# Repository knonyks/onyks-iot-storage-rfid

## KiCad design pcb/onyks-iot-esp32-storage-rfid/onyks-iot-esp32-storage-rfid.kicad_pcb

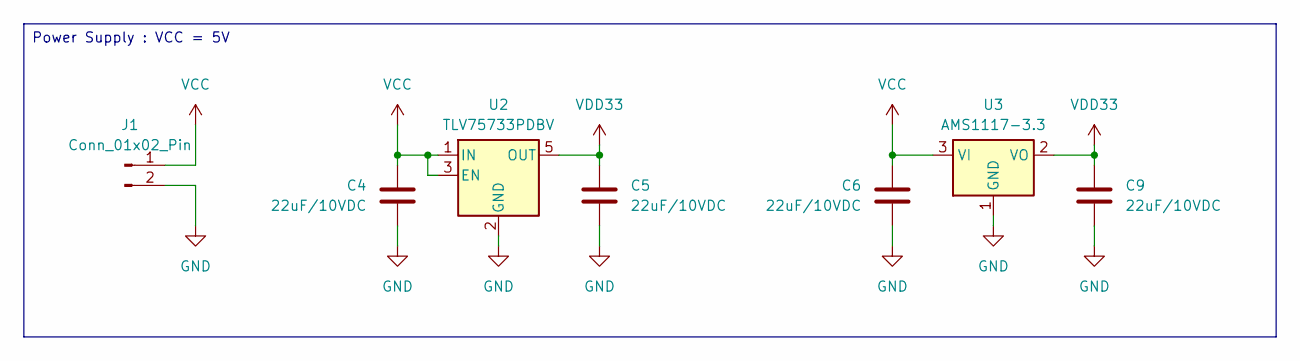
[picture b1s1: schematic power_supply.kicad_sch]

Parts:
C4, C5, C6, C9: 22uF/10VDC; C_0603_1608Metric_Pad1.08x0.95mm_HandSolder
J1: Conn_01x02_Pin; PinHeader_1x02_P2.54mm_Vertical
U2: TLV75733PDBV; SOT-23-5
U3: AMS1117-3.3; SOT-223-3_TabPin2

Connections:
GND: C4.2, C5.2, C6.2, C9.2, J1.2, U2.2 (GND), U3.1 (GND); also elsewhere on the board
VCC: C4.1, C6.1, J1.1, U2.1 (IN), U2.3 (EN), U3.3 (VI); also elsewhere on the board
VDD33: C5.1, C9.1, U2.5 (OUT), U3.2 (VO); also elsewhere on the board

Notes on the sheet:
Power Supply : VCC = 5V

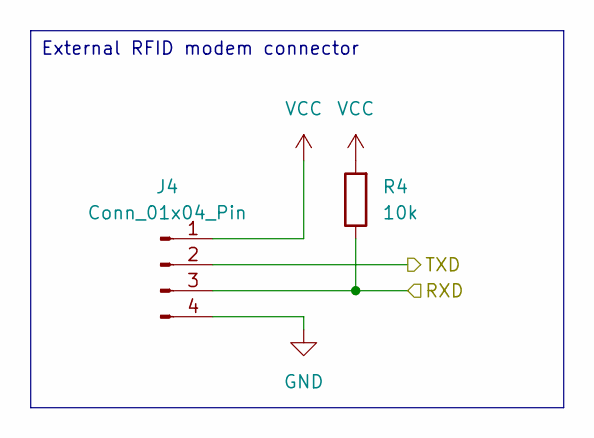
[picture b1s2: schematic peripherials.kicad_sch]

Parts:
J4: Conn_01x04_Pin; PinHeader_1x04_P2.54mm_Vertical
R4: 10k; R_0603_1608Metric_Pad0.98x0.95mm_HandSolder

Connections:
/ESP32/RXD: J4.2; also elsewhere on the board
/ESP32/TXD: J4.3, R4.1; also elsewhere on the board
GND: J4.4; also elsewhere on the board
VCC: J4.1, R4.2; also elsewhere on the board

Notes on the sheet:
External RFID modem connector

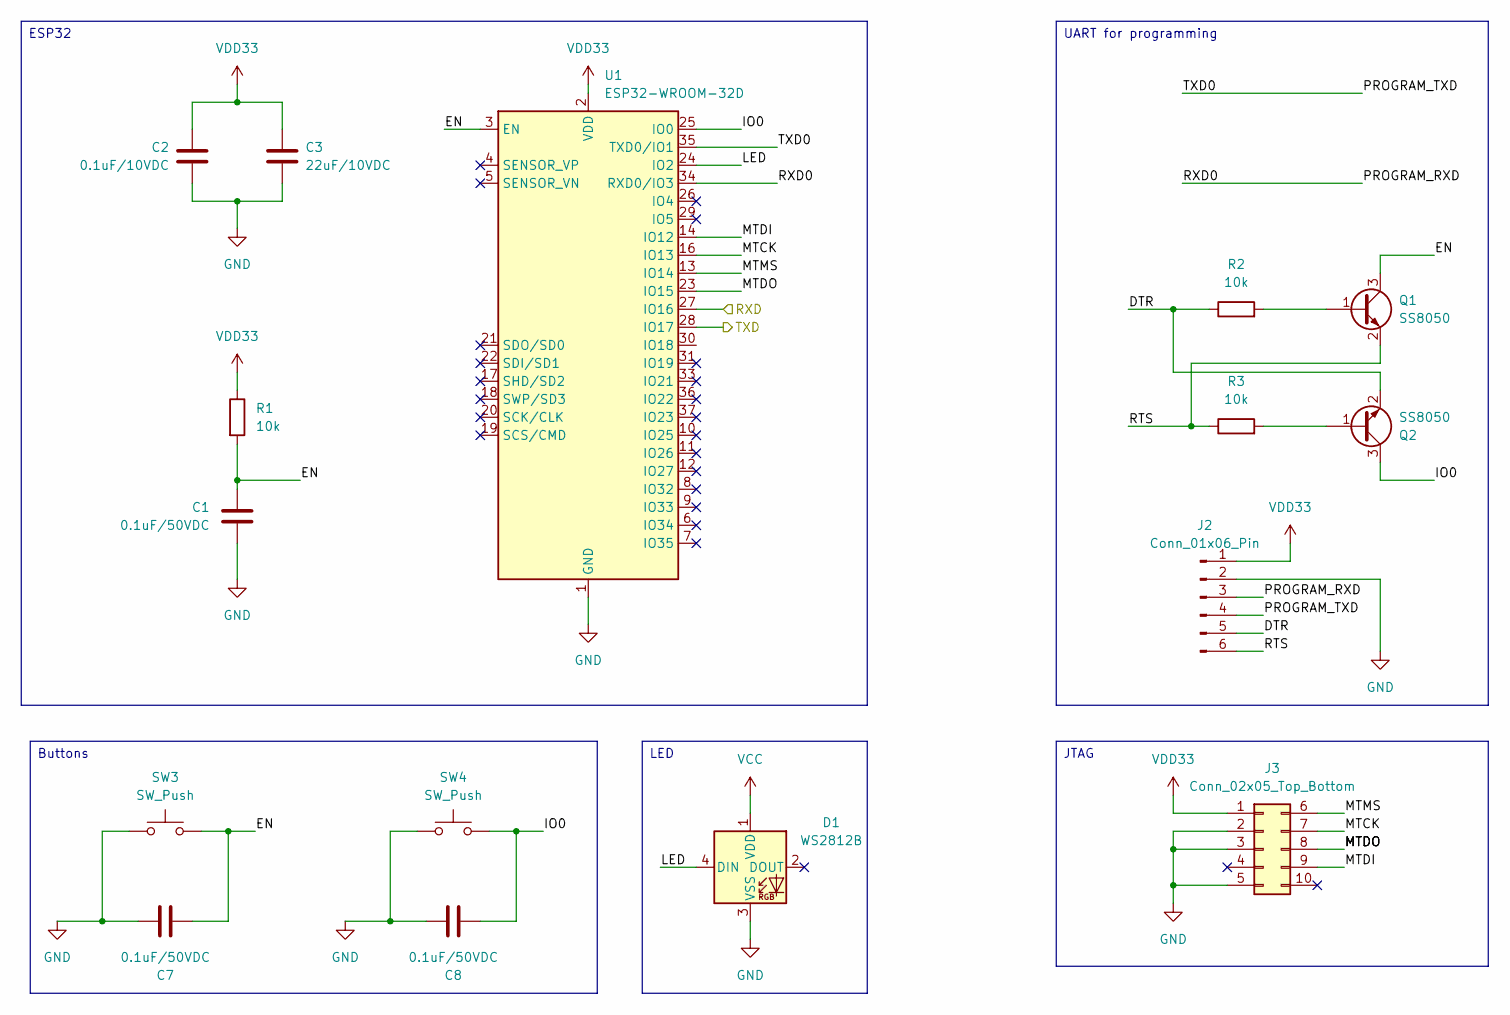
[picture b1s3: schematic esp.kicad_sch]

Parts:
C1, C7, C8: 0.1uF/50VDC; C_0603_1608Metric_Pad1.08x0.95mm_HandSolder
C2: 0.1uF/10VDC; C_0603_1608Metric_Pad1.08x0.95mm_HandSolder
C3: 22uF/10VDC; C_0603_1608Metric_Pad1.08x0.95mm_HandSolder
D1: WS2812B; LED_WS2812B_PLCC4_5.0x5.0mm_P3.2mm
J2: Conn_01x06_Pin; PinHeader_1x06_P2.54mm_Vertical
J3: Conn_02x05_Top_Bottom; PinHeader_2x05_P2.54mm_Vertical
Q1, Q2: SS8050; SOT-23
R1, R2, R3: 10k; R_0603_1608Metric_Pad0.98x0.95mm_HandSolder
SW3, SW4: SW_Push; SW_Tactile_SPST_NO_Straight_CK_PTS636Sx25SMTRLFS
U1: ESP32-WROOM-32D

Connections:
/ESP32/DTR: J2.5, Q2.2 (E), R2.1
/ESP32/EN: C1.2, C7.2, Q1.3 (C), R1.2, SW3.2, U1.3 (EN)
/ESP32/IO0: C8.2, Q2.3 (C), SW4.2, U1.25 (IO0)
/ESP32/LED: D1.4 (DIN), U1.24 (IO2)
/ESP32/MTCK: J3.7, U1.16 (IO13)
/ESP32/MTDI: J3.9, U1.14 (IO12)
/ESP32/MTDO: J3.8, U1.23 (IO15)
/ESP32/MTMS: J3.6, U1.13 (IO14)
/ESP32/PROGRAM_RXD: J2.3, U1.34 (RXD0/IO3)
/ESP32/PROGRAM_TXD: J2.4, U1.35 (TXD0/IO1)
/ESP32/RTS: J2.6, Q1.2 (E), R3.1
/ESP32/RXD: U1.27 (IO16); also elsewhere on the board
/ESP32/TXD: U1.28 (IO17); also elsewhere on the board
GND: C1.1, C2.2, C3.2, C7.1, C8.1, D1.3 (VSS), J2.2, J3.2, J3.3, J3.5, SW3.1, SW4.1, U1.1 (GND), U1.15 (GND), U1.38 (GND), U1.39 (GND); also elsewhere on the board
unnamed: Q1.1 (B), R2.2
unnamed: Q2.1 (B), R3.2
VCC: D1.1 (VDD); also elsewhere on the board
VDD33: C2.1, C3.1, J2.1, J3.1, R1.1, U1.2 (VDD); also elsewhere on the board

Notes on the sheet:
LED
UART for programming
Buttons
JTAG
ESP32

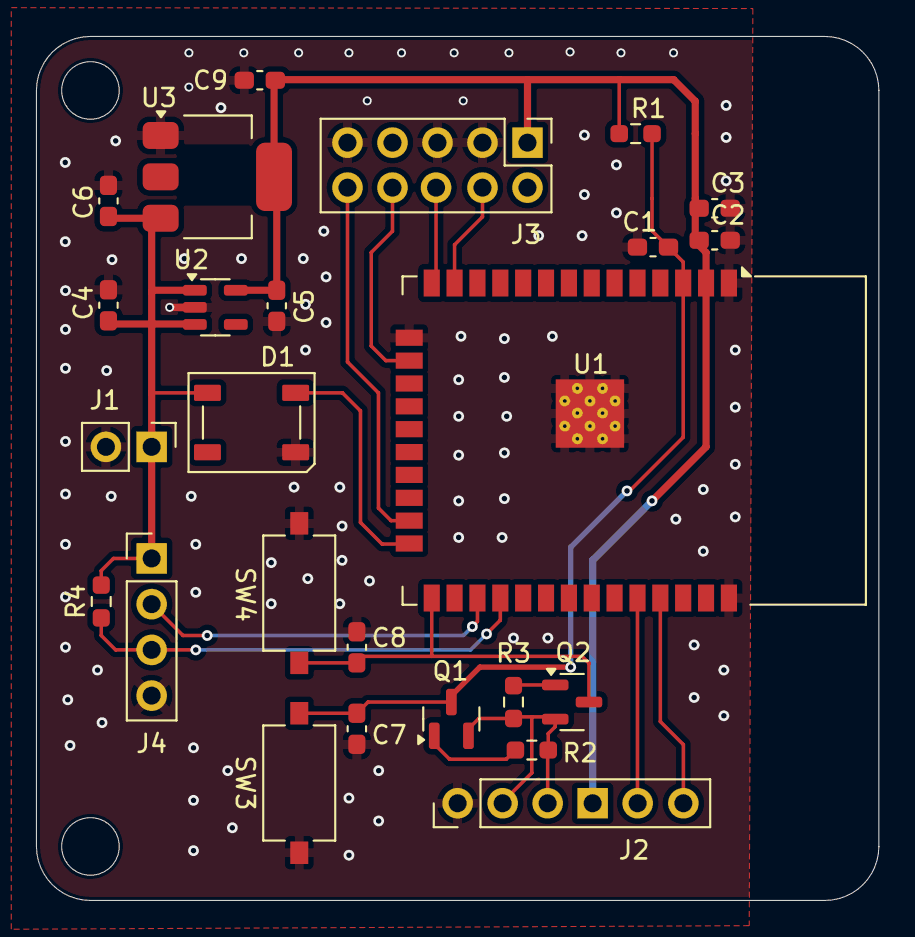
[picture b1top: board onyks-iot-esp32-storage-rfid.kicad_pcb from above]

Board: 4 copper layers, 46.8 x 48.0 mm, 25 parts (0 on the bottom side), 18 nets.

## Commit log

2025-06-27 Pierwszy commit
2025-07-28 Nie pełna lista elementów wykorzystywanych w projekcie. Zrobiony schemat (bez rewizii).
2025-07-28 Zapomniałem o rulesach.
2025-08-20 oznaczenie pinów i podział elementów PCB
    dodanie oznaczenia nieużywanych pinów zgodnie z opinią schematu
2025-08-23 ustawienie i połączenia na PCB
    szerokości ścieżek i wielkości przelotek jeszcze do poprawy
2025-08-31 szerokości ścieżek
2025-09-09 PCB gotowe do review
2025-10-22 projekt PCB v2
2025-10-23 projekt PCB v2.2
    Projekt gotowy do review. @przemech @Xenon02
    Dodany zostal drugi stabilizator AMS1117-3.3, ktory mamy w nadmiarze w kole.
    Zaktualizowano DR na zgodne z JLCPCB capabilities, ktore wczesniej byly bledne.
    Dodano opis wymiarow plytki.
2025-10-23 zrobione review, wprowadzone poprawki, czeka na ostatnie sprawdzenie jak prezes bedzie bardizej przytomny
2025-10-26 Adding Gerber files
2025-10-29 male zmiany PCB
    poprawiono niezmienione przelotki i usunieto powierzchnie masy pod U3
2025-11-16 Aktualizacja gerberów, powiązane z dwoma poprzednimi commit-ami
2025-11-16 Poprawka folderu gdzie gerbery zostały włożone (/pcb/onyks-iot-esp32-storage-rfid/Fabrication a powinno być /Fabrication)
2026-03-23 dokumentacja plytki v1.0
2026-03-23 dokumentacja v1.1
    dodanie zdjęcia płytki PCB i poprawa adresacji pliku BOM.html
2026-04-15 kod ESP32 v0.0
    program przykładowy, test działania układu
2026-04-16 dokumentacja v1.2
    porządek w plikach i datasheet ESP32
2026-05-06 kod ESP32 v0.1
    konfiguracja diody i uart dla R200
2026-05-09 kod ESP32 v0.2
    klasa UART i funkcja wysylajaca ramki do R200
2026-05-19 kod ESP32 v0.3
    zmiany w klasie R200, funkcje wysyłające i odbierające ramki do R200, obsługa tasków w freeRTOS
